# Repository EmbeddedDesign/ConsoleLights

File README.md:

# ConsoleLights
Tardis Console Button and Light Controller

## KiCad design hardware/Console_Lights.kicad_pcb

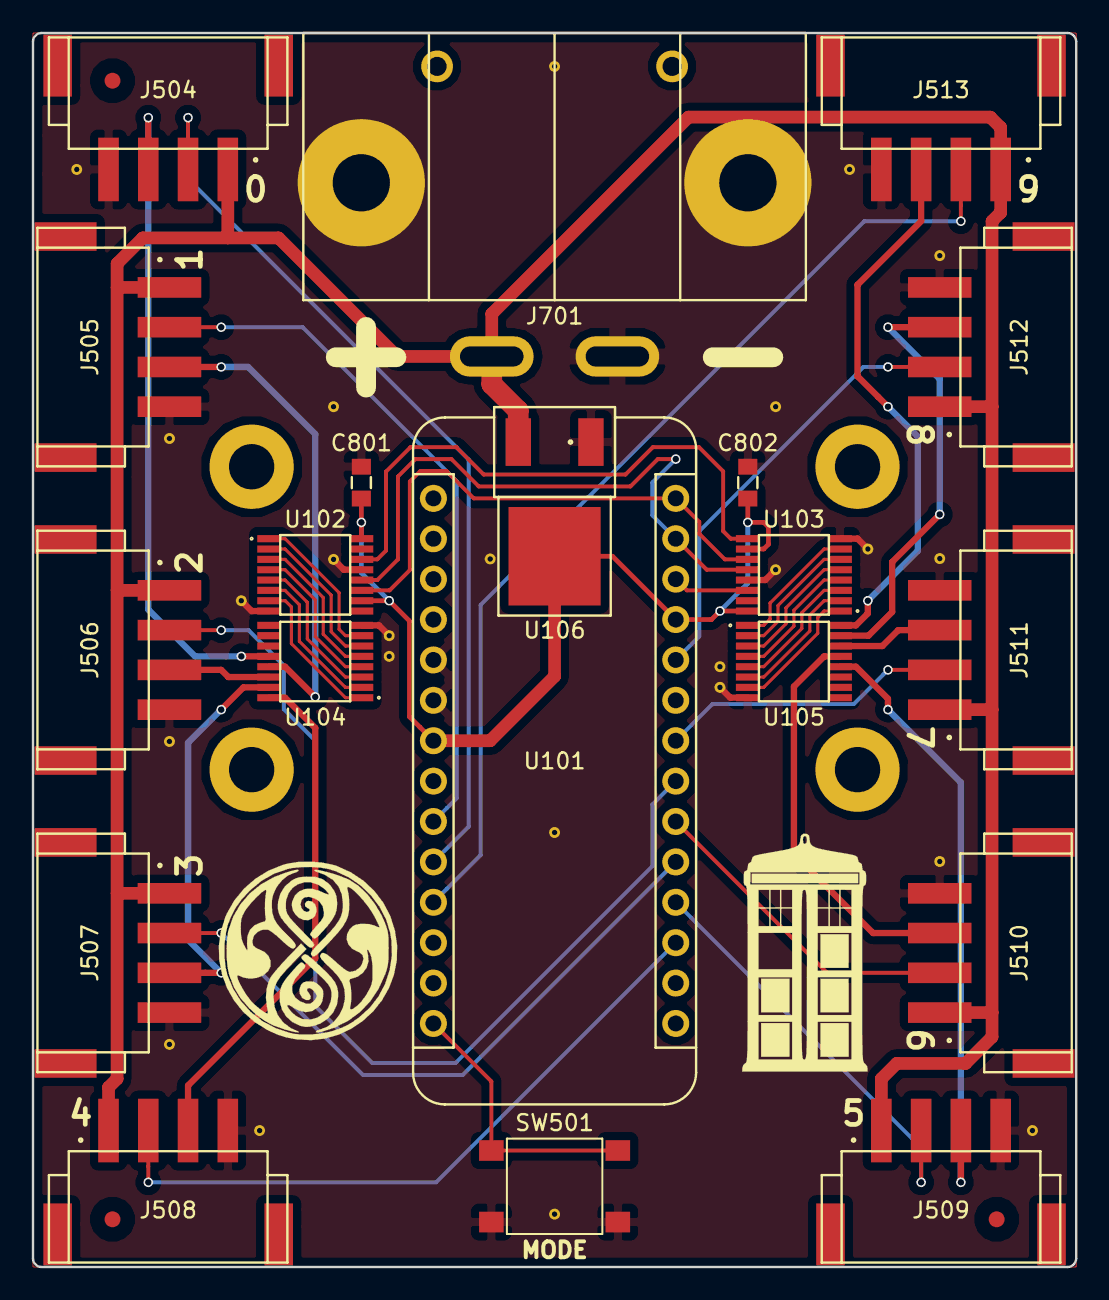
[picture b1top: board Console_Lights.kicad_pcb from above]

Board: 2 copper layers, 65.6 x 77.6 mm, 23 parts (0 on the bottom side), 42 nets.

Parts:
C801, C802: 1uF; C_0603
J504, J505, J506, J507, J508, J509, J510, J511, J512, J513: JST_Conn; S4B-XH-SM4-TB
J701: Conn_01x02; ASMPR45-1X2-RK_Wings
SW501: SWITCH; CK_PTS645_Tac_Switch
U101: Metro_Mini
U102, U103: 74HC595_SHIFT_REGISTER; 16-TSSOP
U104, U105: ULN2003A_DARLINGTON_ARRAY; 16-TSSOP
U106: NCP1117-5_DPAK; DPAK_TO-252
fid1, fid2, fid3: FID; Fiducial

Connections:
+5V: C801.1, C802.1, U101.10, U101.26, U102.10, U102.16, U103.10, U103.16, U106.2
+12V: J504.1, J505.1, J506.1, J507.1, J508.1, J509.1, J510.1, J511.1, J512.1, J513.1, J701.1, U106.3
/CLOCK: U101.13, U102.11, U103.11
/DATA: U101.11, U103.14
/LATCH: U101.12, U102.12, U103.12
/LED_0: J504.3, U104.12
/LED_1: J505.3, U104.13
/LED_2: J506.3, U104.14
/LED_3: J507.3, U104.15
/LED_4: J508.3, U104.16
/LED_5: J509.3, U105.12
/LED_6: J510.3, U105.13
/LED_7: J511.3, U105.14
/LED_8: J512.3, U105.15
/LED_9: J513.3, U105.16
/MODE: SW501.2, U101.19
/SWITCH_0: J504.2, U101.15
/SWITCH_1: J505.2, U101.14
/SWITCH_2: J506.2, U101.6
/SWITCH_3: J507.2, U101.4
/SWITCH_4: J508.2, U101.2
/SWITCH_5: J509.2, U101.3
/SWITCH_6: J510.2, U101.5
/SWITCH_7: J511.2, U101.7
/SWITCH_8: J512.2, U101.9
/SWITCH_9: J513.2, U101.16
GND: C801.2, C802.2, J504.4, J505.4, J506.4, J507.4, J508.4, J509.4, J510.4, J511.4, J512.4, J513.4, J701.2, SW501.1, U101.24, U101.25, U102.8, U102.13, U103.8, U103.13, U104.8, U105.8, U106.1
unnamed: U102.1, U104.7
unnamed: U102.2, U104.6
unnamed: U102.3, U104.5
unnamed: U102.4, U104.4
unnamed: U102.5, U104.3
unnamed: U102.6, U104.2
unnamed: U102.7, U104.1
unnamed: U102.14, U103.9
unnamed: U103.1, U105.7
unnamed: U103.2, U105.6
unnamed: U103.3, U105.5
unnamed: U103.4, U105.4
unnamed: U103.5, U105.3
unnamed: U103.6, U105.2
unnamed: U103.7, U105.1

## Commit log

2018-10-31 creat lib, add footprints, schematic updates
2018-11-02 add footprints, BOM, schematic updates
2018-11-07 BOM, footprint updates
2018-11-09 add regulator, BOM, schematic, layout updates
2018-11-10 mounting plate outline, floor-planning
2018-11-29 schematic/routing update
2018-11-30 routing updates
2018-11-30 routing updates, logo
2018-12-07 shcematic/routing updates, add fab notes
2018-12-13 layout updates
2018-12-14 add seal, prints, production files
2018-12-18 production file update
2018-12-19 bringup test code
2019-01-02 add quick-connects to BOM
2019-01-06 quick connect update
2019-01-09 application/feature updates
2019-01-10 optimization, code cleanup, comments
2019-01-23 cleanup, add interrupt based test code
2019-01-26 interrupt based code, cleanup
2019-01-26 quick connect wiring diagram
2019-01-29 slightly faster, more efficient code, onOff bug fix
